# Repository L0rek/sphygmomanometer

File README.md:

### Blood pressure measurement by means of red light absorption.

Chip: [stm32 Blue Pill](https://wiki.stm32duino.com/index.php?title=Blue_Pill)

Light Sensor: [VEML7700](https://www.vishay.com/docs/84286/veml7700.pdf)

LED: SMD 1206R Red 637nm

Pressure Sensor: ----

Pomp: Micro Air Pump

Valve: Solenoid Valve

### Usefull

Add stm32 lib to Arduino [Getting-Started](https://github.com/stm32duino/wiki/wiki/Getting-Started)

Change to usb boot loader [Burning-the-bootloader](https://wiki.stm32duino.com/index.php?title=Burning_the_bootloader)

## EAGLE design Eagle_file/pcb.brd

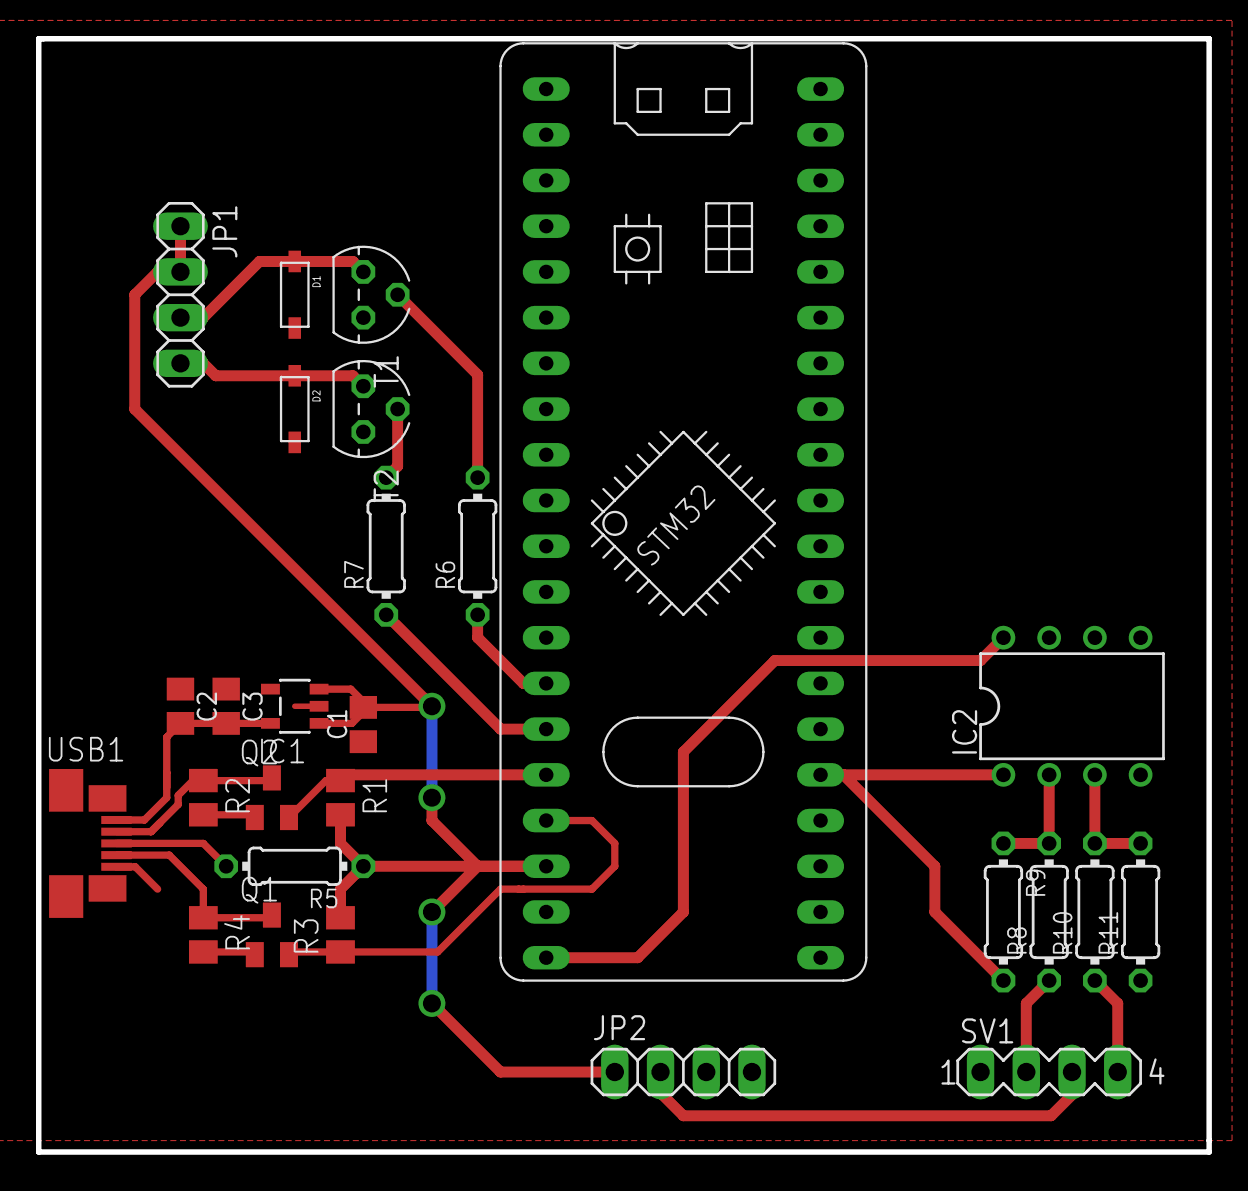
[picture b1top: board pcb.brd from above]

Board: 2 copper layers, 65.0 x 61.8 mm, 27 parts (0 on the bottom side), 23 nets.

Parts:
C1, C2: 10uF; C-0805
C3: 100nF; C-0805
D1, D2: SOD-123
IC1: BL8555-33; SOT23-5
IC2: LM358N; DIL08
JP1: 1X04
JP2: Step Up; 1X04
Q1, Q2: SOT23
R1, R2, R4: 4.7K; M0805
R3: 4.7; M0805
R5: 250; 0204/7
R6, R7: 1K; 0204/7
R8, R10: 100k; 0204/7
R9, R11: 1M; 0204/7
SV1: MPX2050; MA04-1
T1, T2: BC547; TO92
U$1: stm32f103c8t6; BLUE_PILL
USB1: MOLEX-47346-0001; MOLEX-47364-0001

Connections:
3.3V: IC2.8, U$1.P$20
3.3VS: C2.2, C3.2, IC1.5, USB1.1
10V: JP2.2, SV1.3
GND: C1.1, C2.1, C3.1, D1.A, D2.A, IC1.2, IC2.4, JP2.3, JP2.4, R11.1, SV1.1, T1.1, T2.1, U$1.P$19, U$1.P$21, U$1.P$22, USB1.5, USB1.GND1, USB1.GND2, USB1.GND3, USB1.GND4
LED: R5.2, USB1.3
unnamed: D2.C, JP1.4, T2.3
unnamed: Q1.1, R4.2
unnamed: D1.C, JP1.3, T1.3
unnamed: R7.2, T2.2
unnamed: Q2.1, R2.2
unnamed: R6.2, T1.2
unnamed: Q2.3, R2.1, USB1.2
unnamed: IC2.2, R8.2, R9.1
unnamed: IC2.3, R10.2, R11.2
PA0: IC2.1, R9.2, U$1.P$36
PB6: R6.1, U$1.P$14
PB7: R7.1, U$1.P$15
PB8: Q2.2, R1.1, U$1.P$16
PB9: Q1.2, R3.1, U$1.P$17
SDA: Q1.3, R4.1, USB1.4
V+: R8.1, SV1.2
V-: R10.1, SV1.4
VCC: C1.2, IC1.1, IC1.3, JP1.1, JP1.2, JP2.1, R1.2, R3.2, R5.1, U$1.P$18

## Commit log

2018-11-28 change dir
2018-11-28 change name
2018-11-29 add schemate
2018-11-29 Updata
2018-12-03 Update pcb board
2018-12-19 Add datafilter and up

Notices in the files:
parts and their libraries:
cap-pan40: Copyright (C) 2004, Bob Starr
